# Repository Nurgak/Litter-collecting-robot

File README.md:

# STI interdisciplinary robot competitionThis project was completed as a Master semester project at [École polytechnique fédérale de Lausanne](http://www.epfl.ch).* Authors: Karl Kangur, Marcel Starein, Chun Xie* Assistants: Alessandro Crespi, Gorecki Tomasz* Professor: Auke Ijspeert## AbstractThe [STI competition](http://robot-competition.epfl.ch) is a interdisciplinary Master semester project in form of a competition between five teams of three people from different educational backgrounds. The competition's goal is to design and build a litter collecting robot and outperform the other robots. The teams are given funds in order to buy parts, order custom parts from the in-house mechanics or make use of the available 3D printers.## Project reportThe complete project report with all the documentation is in `Documents/Project report.pdf`.## Video[**Video of bottle fetching and detection demonstration**](https://www.youtube.com/watch?v=RZNW9JzXmiI)## PicturesSee under `Photos`.## Files* All documents related to the project (rules, deadlines) and the project report itself are in `Documents`* Documents related to sensors are under `Datasheets`* First concepts in Google SketchUp, final parts in SolidWorks format and custom PCBs in `Hardware`* The complete source code for the Raspberry Pi, Arduino code for the [PRsimino](https://github.com/Robopoly/prismino) and the custom WildThumper motor controller are in `Software`* Pictures of the robot are under `Photos`* The Webots files for the simulation are in `Webots simulation`

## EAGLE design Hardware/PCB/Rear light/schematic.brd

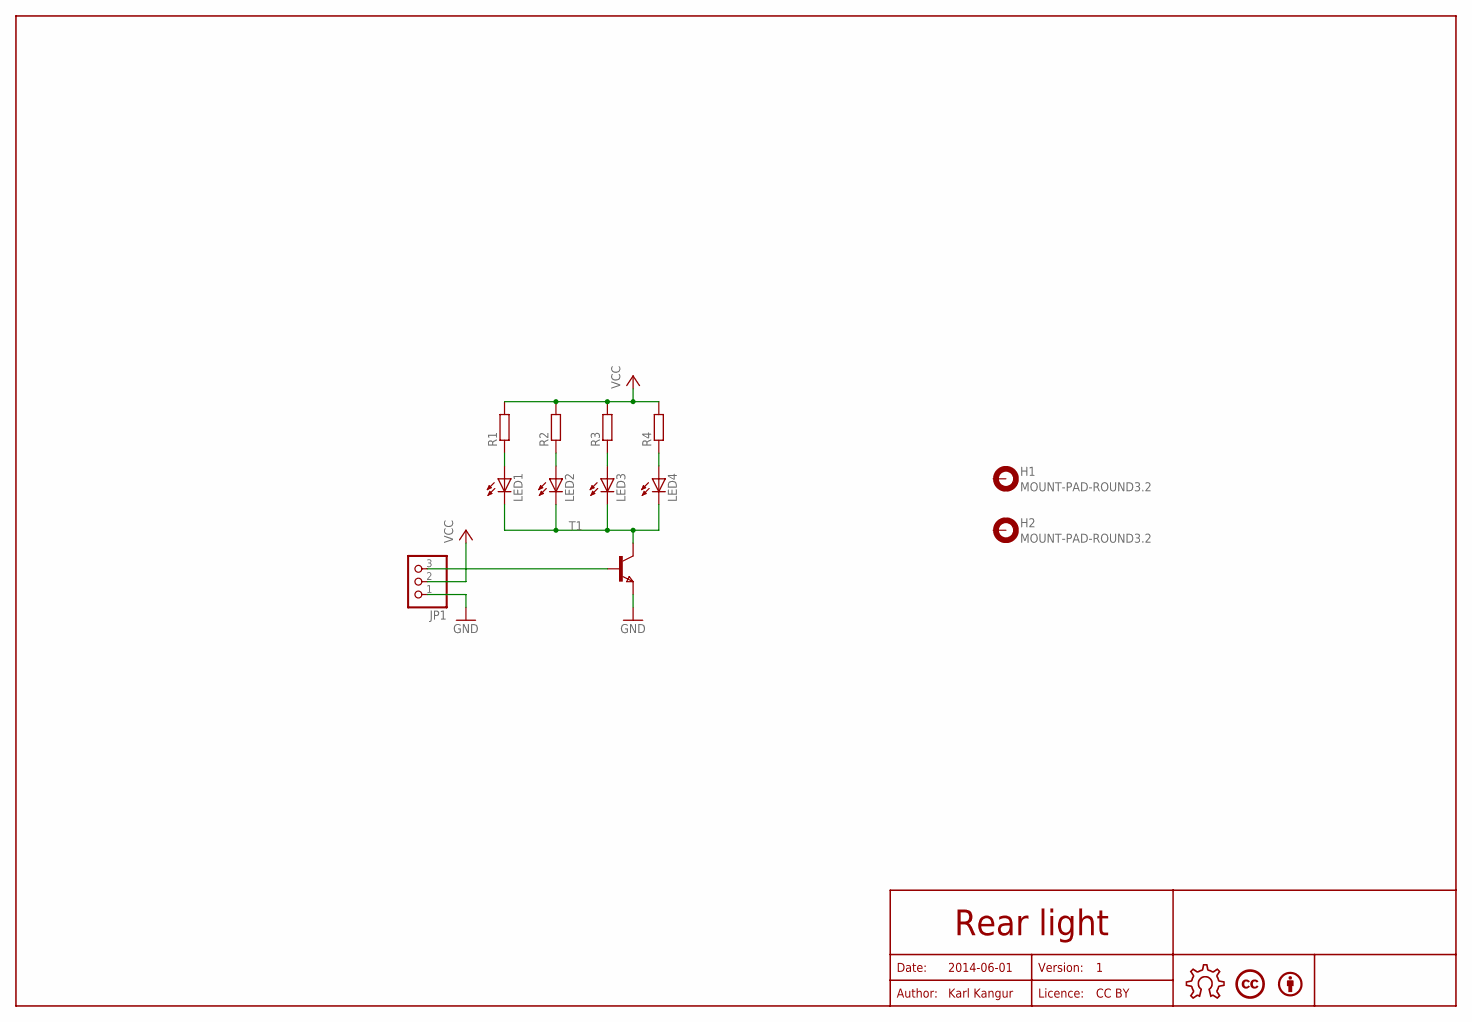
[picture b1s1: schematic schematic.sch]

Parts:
BY1: BYBOTTOM; BY
H1, H2: MOUNT-PAD-ROUND3.2; 3,2-PAD
JP1: PINHD-1X3; 1X03
LED1, LED2, LED3, LED4: LED3MM
LICENCE1: LICENCECC-BOTTOM; CREATIVE-COMMONS
R1, R2, R3, R4: R-EU_R0805; R0805
T1: NPNSOT323; SOT323
U$10: OPEN-HARDWARE-LOGOBOTTOM-SMALL; OPEN-HARDWARE-BOTTOM-SMALL

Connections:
GND: JP1.1, T1.3 (E)
unnamed: JP1.3, T1.2 (B)
unnamed: LED1.K (C), LED2.K (C), LED3.K (C), LED4.K (C), T1.1 (C)
unnamed: LED1.A, R1.1
unnamed: LED2.A, R2.1
unnamed: LED3.A, R3.1
unnamed: LED4.A, R4.1
VCC: JP1.2, R1.2, R2.2, R3.2, R4.2

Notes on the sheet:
Date:
Author:
Licence:
Version:
2014-06-01
Karl Kangur
CC BY
Rear light

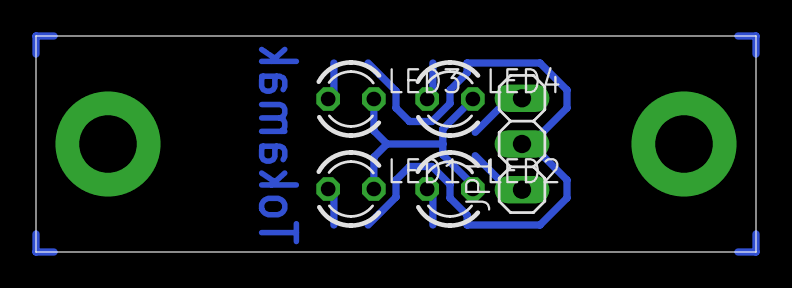
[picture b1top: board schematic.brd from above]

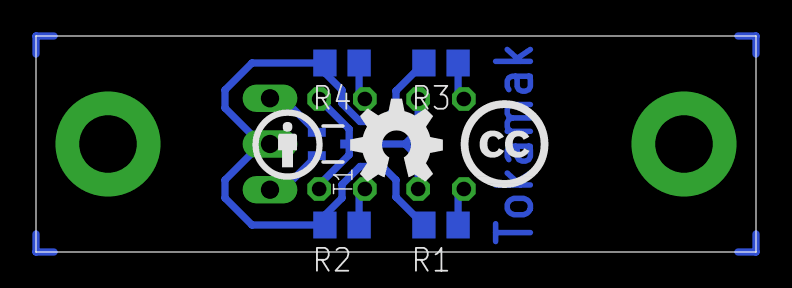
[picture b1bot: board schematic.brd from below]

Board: 2 copper layers, 40.0 x 12.0 mm, 15 parts (5 on the bottom side), 8 nets.

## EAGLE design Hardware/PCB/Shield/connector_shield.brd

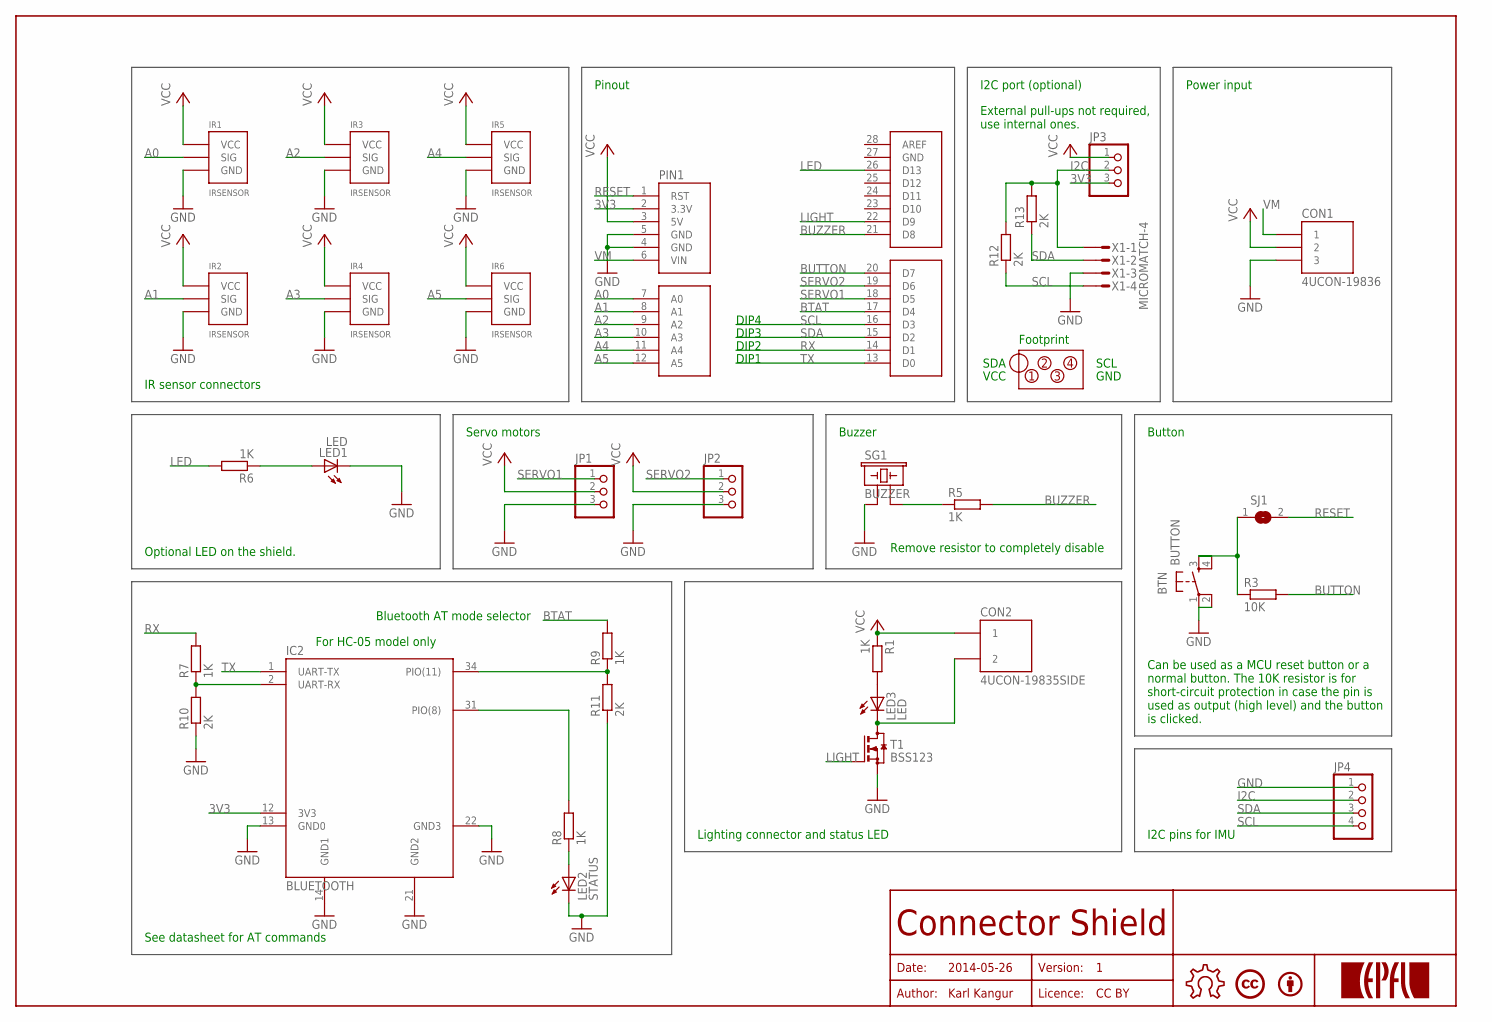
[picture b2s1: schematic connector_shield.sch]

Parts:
BTN: BUTTON
BY1: BYBOTTOM; BY
CON1: 4UCON-19836
CON2: 4UCON-19835SIDE; 4UCON-19835
IC2: BLUETOOTH
IR1, IR2, IR3, IR4, IR5, IR6: IRSENSOR; A-6373-03
JP1, JP2, JP3: PINHD-1X3; 1X03
JP4: PINHD-1X4; 1X04
LED1, LED3: LED; CHIPLED_0805
LED2: STATUS; CHIPLED_0805
LICENCE1: LICENCECC-BOTTOM; CREATIVE-COMMONS
PIN1: ARDUINOSTACK; ARDUINO-LONG
R1, R5, R6, R7, R8, R9: 1K; R0805
R3: 10K; R0805
R10, R11, R12, R13: 2K; R0805
SG1: BUZZER; PS1240P02BT
SJ1: SJ
T1: BSS123; SOT23
U$10: OPEN-HARDWARE-LOGOBOTTOM-SMALL; OPEN-HARDWARE-BOTTOM-SMALL
U$11: EPFL-LOGO; EPFL-LOGO-PCB
X1: MICROMATCH-4

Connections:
3V3: IC2.12 (3V3), JP3.3, PIN1.2 (3.3V)
A0: IR1.SIG, PIN1.7 (A0)
A1: IR2.SIG, PIN1.8 (A1)
A2: IR3.SIG, PIN1.9 (A2)
A3: IR4.SIG, PIN1.10 (A3)
A4: IR5.SIG, PIN1.11 (A4)
A5: IR6.SIG, PIN1.12 (A5)
BTAT: PIN1.17 (D4), R9.2
BUTTON: PIN1.20 (D7), R3.2
BUZZER: PIN1.21 (D8), R5.2
GND: BTN.1, BTN.2, CON1.3, IC2.13 (GND0), IC2.14 (GND1), IC2.21 (GND2), IC2.22 (GND3), IR1.GND, IR2.GND, IR3.GND, IR4.GND, IR5.GND, IR6.GND, JP1.3, JP2.3, JP4.1, LED1.C, LED2.C, PIN1.4 (GND), PIN1.5 (GND), PIN1.27 (GND), R10.1, R11.1, SG1.P$1 (1), T1.2 (S), X1.3
I2C: JP3.2, JP4.2, R12.2, R13.2, X1.1
LED: PIN1.26 (D13), R6.2
LIGHT: PIN1.22 (D9), T1.1 (G)
unnamed: CON2.2, LED3.C, T1.3 (D)
unnamed: IC2.31 (PIO(8)), R8.2
unnamed: LED2.A, R8.1
unnamed: LED3.A, R1.2
unnamed: R5.1, SG1.P$2 (2)
unnamed: IC2.34 (PIO(11)), R9.1, R11.2
unnamed: LED1.A, R6.1
unnamed: BTN.3, BTN.4, R3.1, SJ1.1
unnamed: IC2.2 (UART-RX), R7.1, R10.2
RESET: PIN1.1 (RST), SJ1.2
RX: PIN1.14 (D1), R7.2
SCL: JP4.4, PIN1.16 (D3), R12.1, X1.4
SDA: JP4.3, PIN1.15 (D2), R13.1, X1.2
SERVO1: JP1.1, PIN1.18 (D5)
SERVO2: JP2.1, PIN1.19 (D6)
TX: IC2.1 (UART-TX), PIN1.13 (D0)
VCC: CON1.2, CON2.1, IR1.VCC, IR2.VCC, IR3.VCC, IR4.VCC, IR5.VCC, IR6.VCC, JP1.2, JP2.2, JP3.1, PIN1.3 (5V), R1.1
VM: CON1.1, PIN1.6 (VIN)

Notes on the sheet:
Date:
Author:
Licence:
Version:
2014-05-26
Karl Kangur
CC BY
Connector Shield
Pinout
I2C port (optional)
Buzzer
Servo motors
Button
DIP1
DIP2
DIP3
DIP4
Power input
See datasheet for AT commands
Footprint
VCC
SDA
SCL
GND
Bluetooth AT mode selector
For HC-05 model only
Can be used as a MCU reset button or a normal button. The 10K resistor is for short-circuit protection in case the pin is used as output (high level) and the button is clicked.
Optional LED on the shield.
External pull-ups not required, use internal ones.
Remove resistor to completely disable
Lighting connector and status LED
IR sensor connectors
I2C pins for IMU

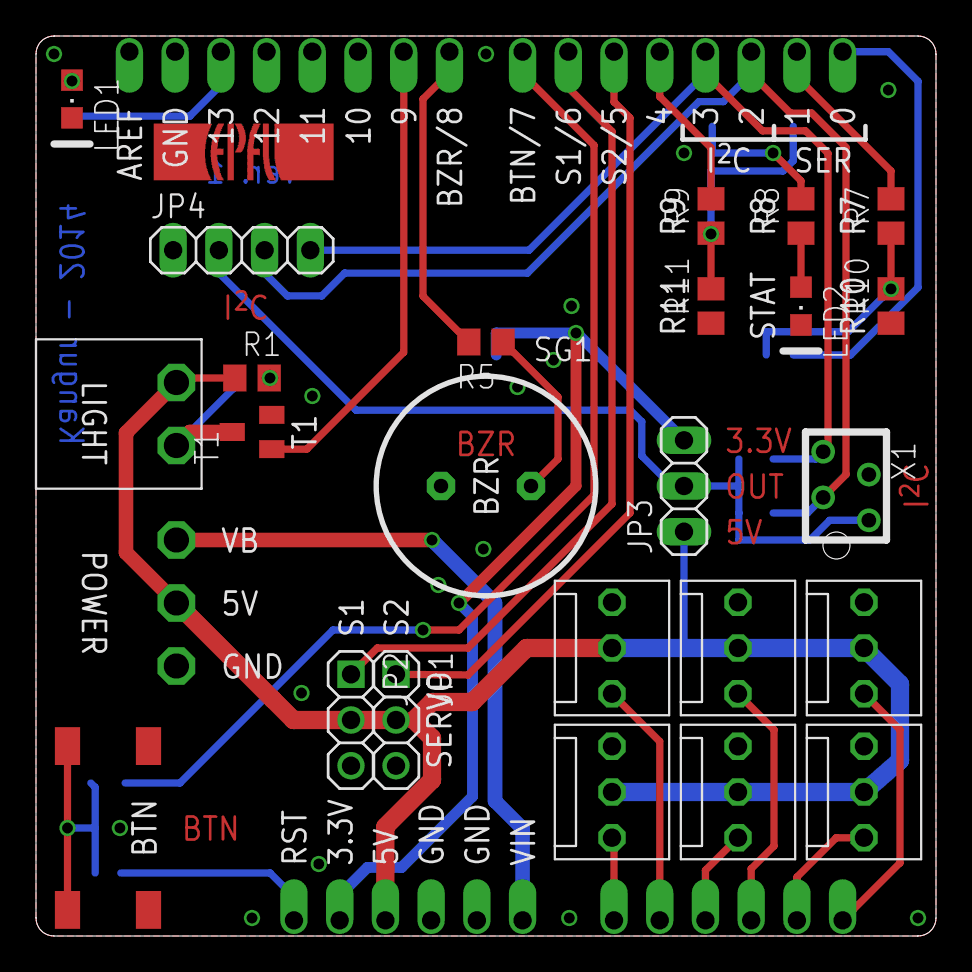
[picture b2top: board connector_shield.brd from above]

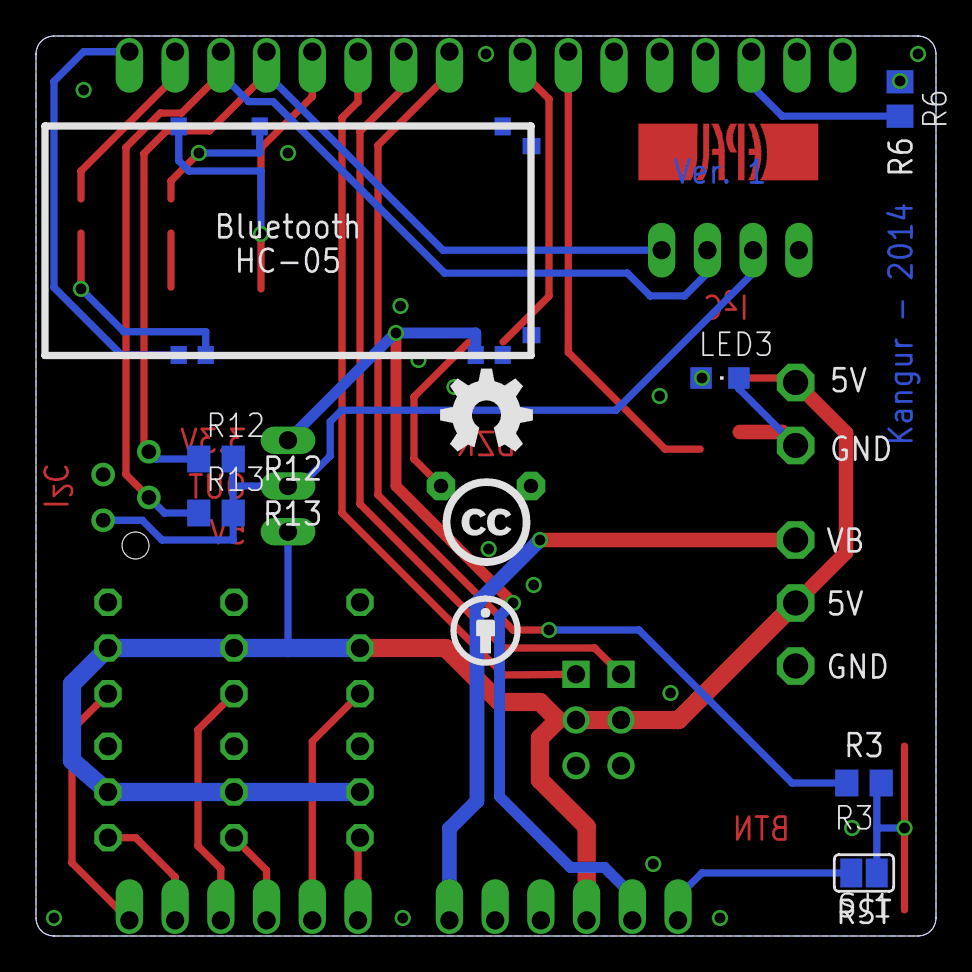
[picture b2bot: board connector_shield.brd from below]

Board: 2 copper layers, 50.0 x 50.0 mm, 37 parts (7 on the bottom side), 32 nets.

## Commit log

2014-06-11 Readme update

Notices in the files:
Hardware/PCB/Shield/connector_shield.brd:
Licence: CC-BY
